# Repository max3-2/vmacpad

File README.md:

# vmacpad

A custom macro pad especially suited for FCPX and any other thing that needs
scrolling!

## ToDos from an old project

- Improve plate manufacture or / and increase switch opening size. The current
dimensioning is ok but fairly tight.
- Do the same for the stabs, if possible add at least 1mm left / right for the
stems

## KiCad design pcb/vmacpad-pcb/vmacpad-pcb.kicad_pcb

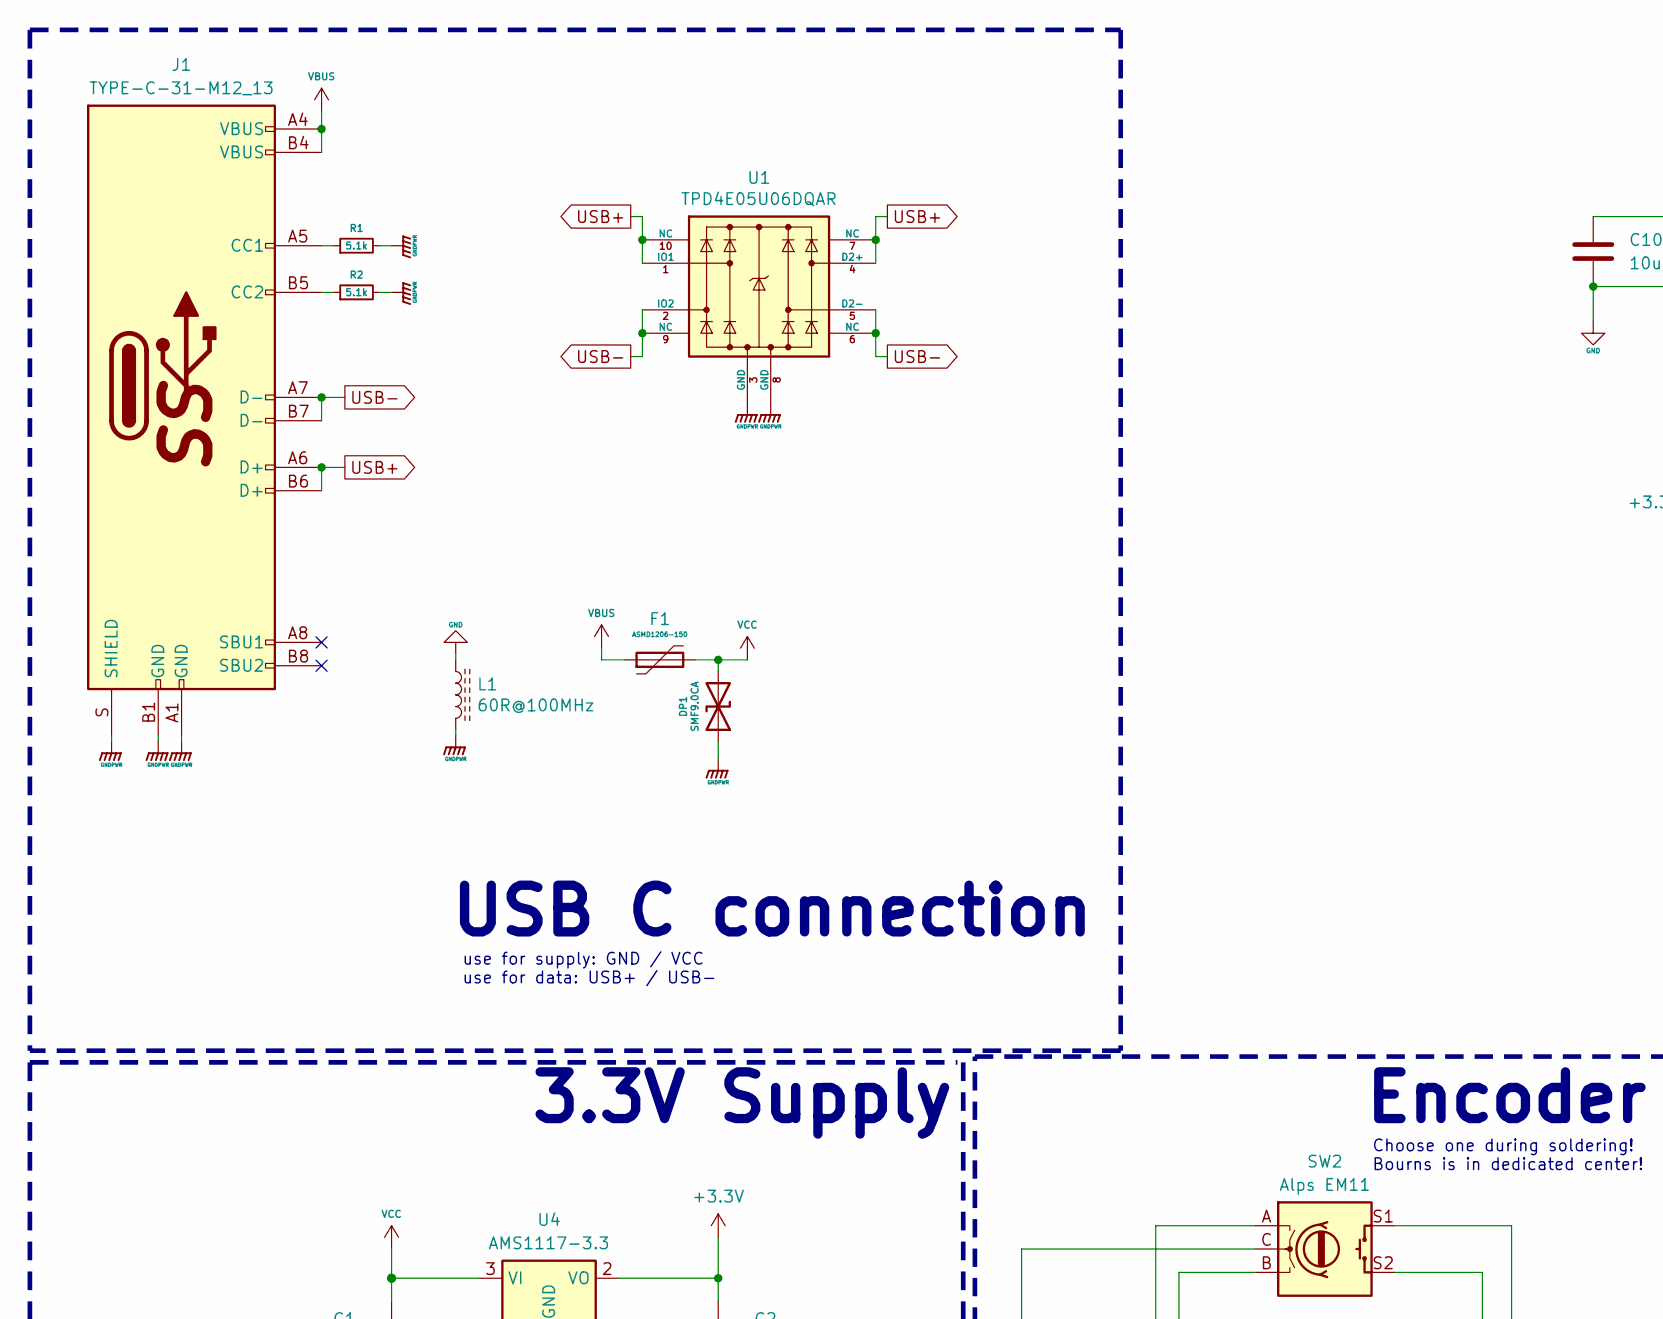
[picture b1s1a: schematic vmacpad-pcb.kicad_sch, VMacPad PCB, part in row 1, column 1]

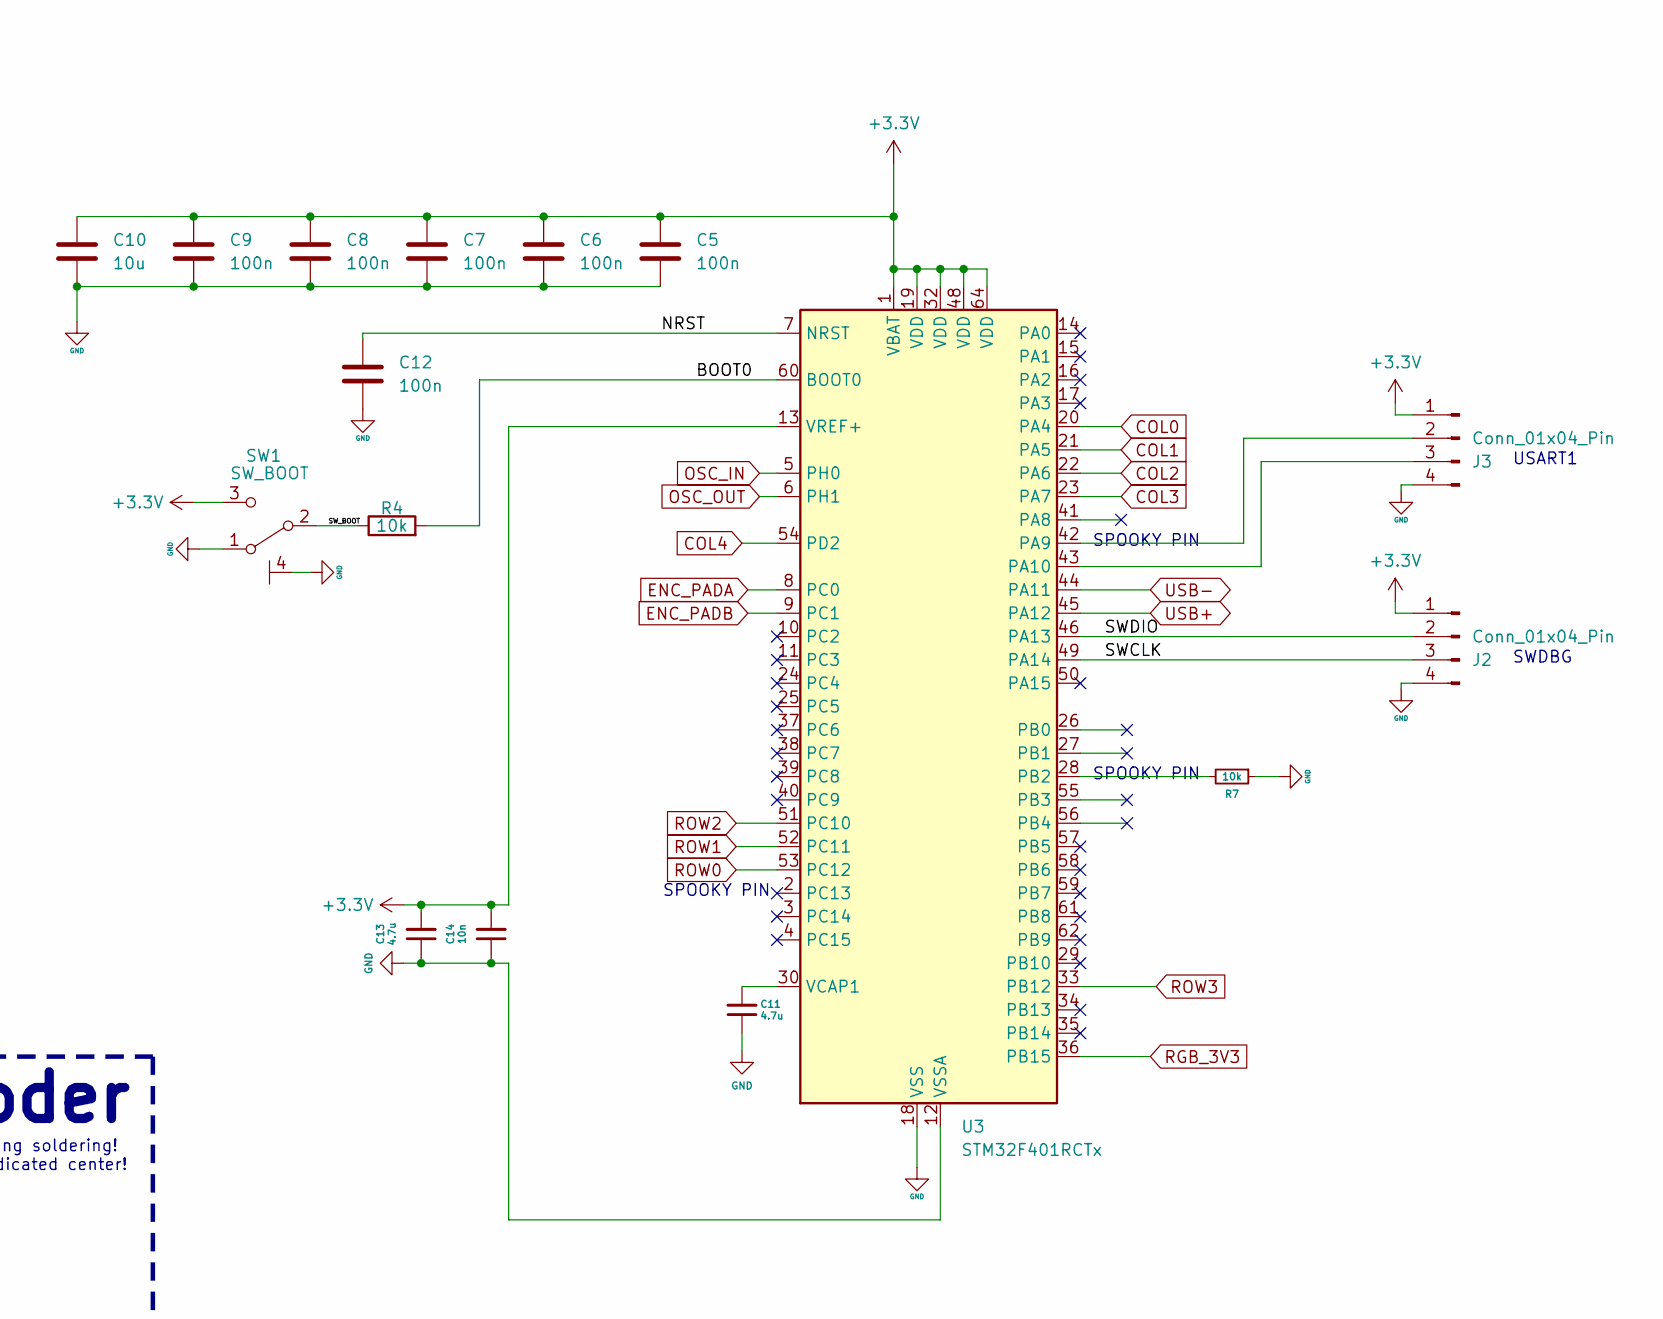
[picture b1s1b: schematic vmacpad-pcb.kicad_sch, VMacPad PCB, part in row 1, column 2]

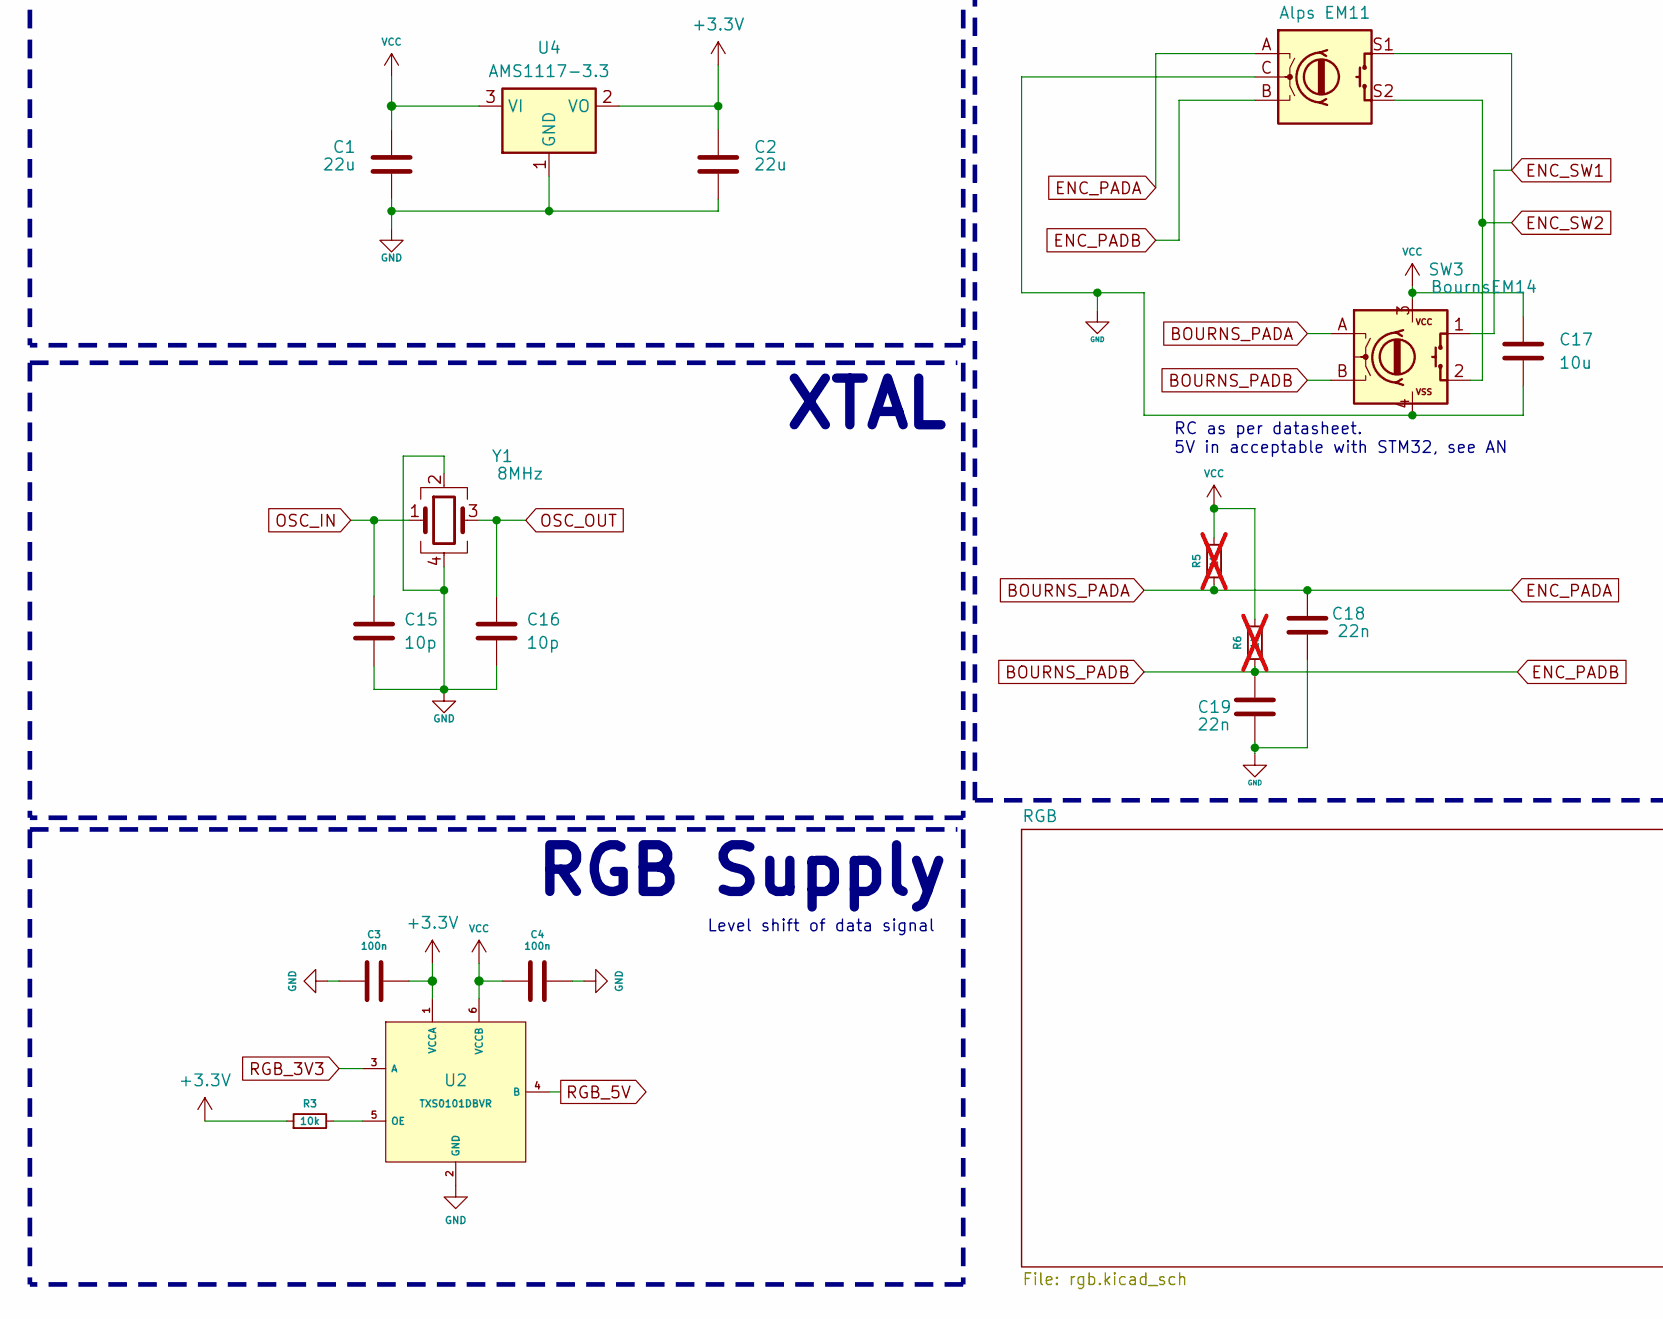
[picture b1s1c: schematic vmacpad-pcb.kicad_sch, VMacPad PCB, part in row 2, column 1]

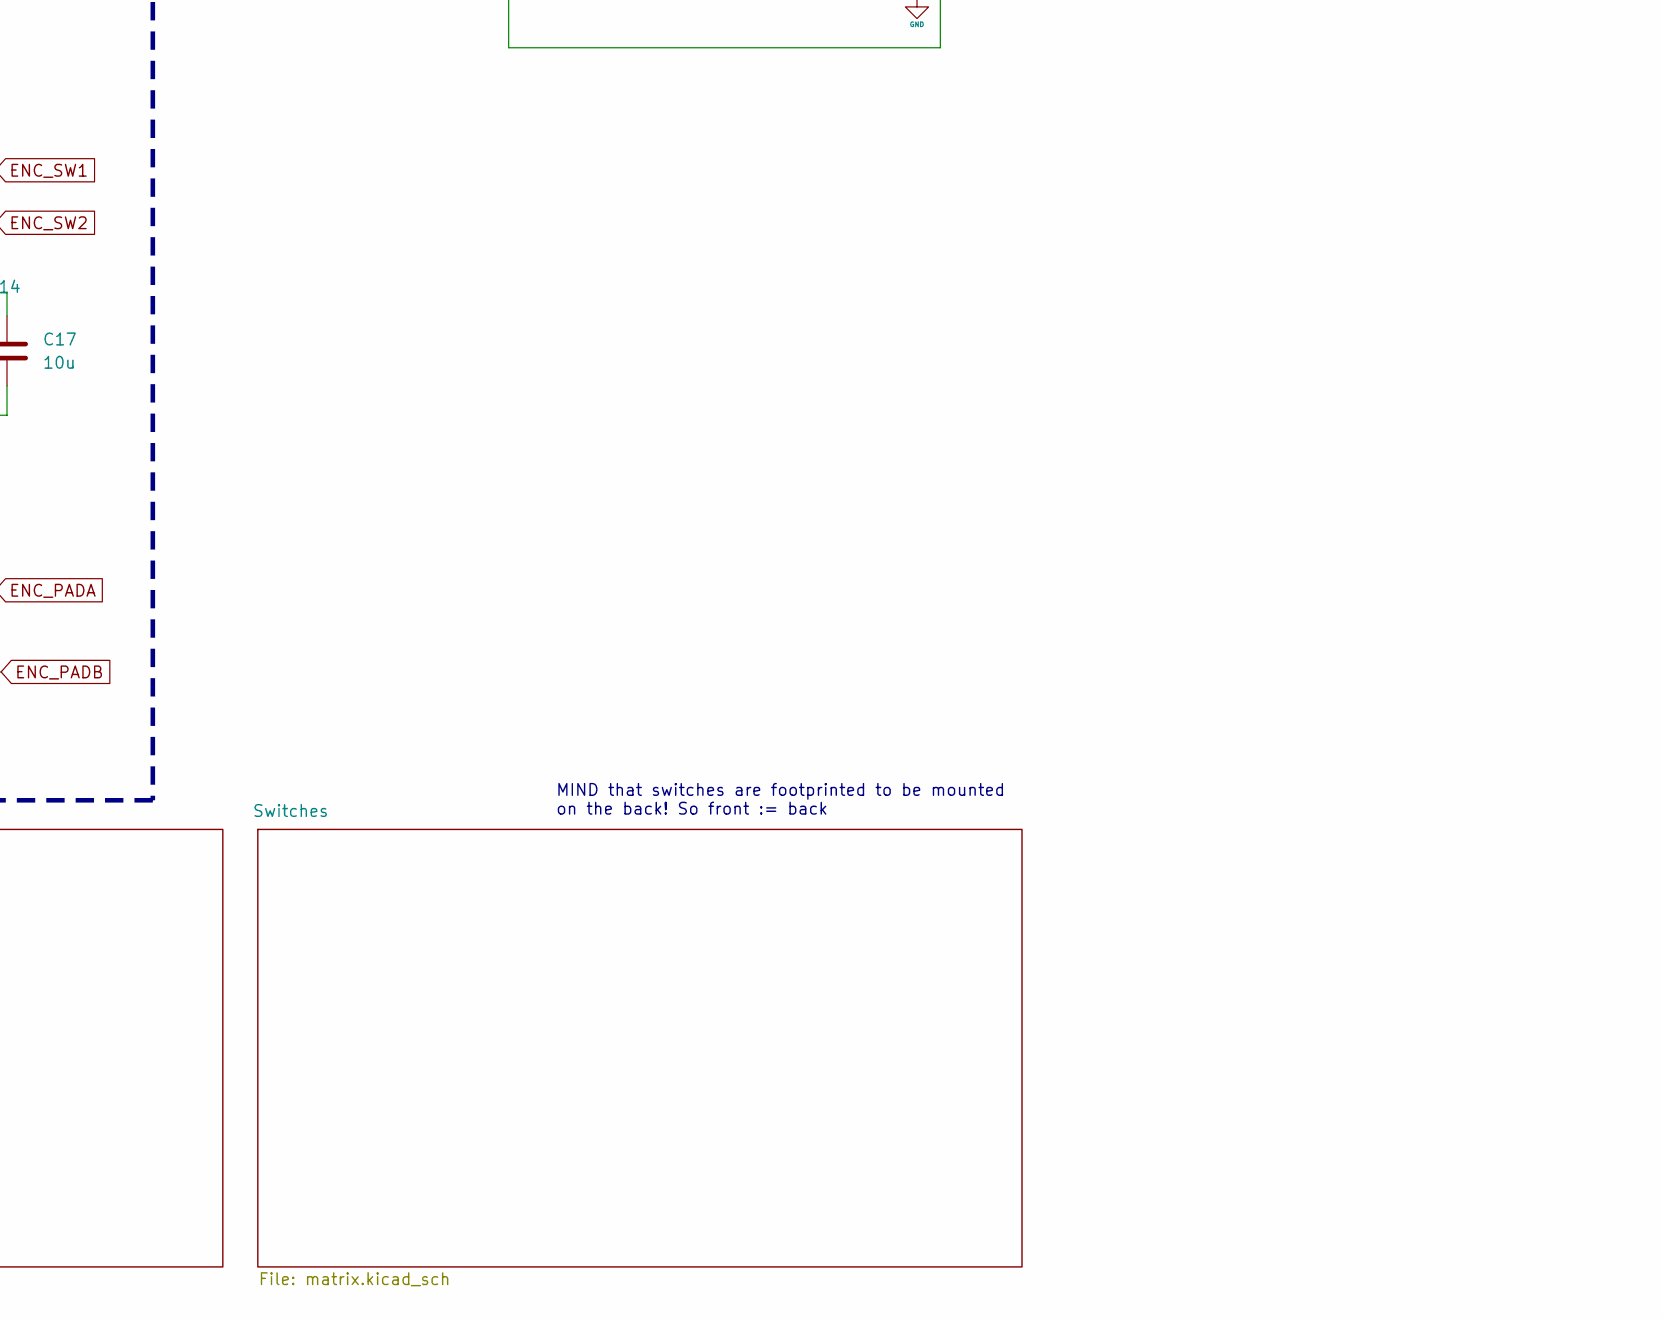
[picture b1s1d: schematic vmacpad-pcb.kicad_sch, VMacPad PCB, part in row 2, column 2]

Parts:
C1, C2: 22u; C_1206_3216Metric; LCSC Part No C2858005
C3, C4, C5, C6, C7, C8, C9, C12: 100n; C_0402_1005Metric; LCSC Part No C77020
C10, C17: 10u; C_0805_2012Metric; LCSC Part No C88484
C11, C13: 4.7u; C_0402_1005Metric; LCSC Part No C368809
C14: 10n; C_0402_1005Metric; LCSC Part No C60133
C15, C16: 10p; C_0402_1005Metric; LCSC Part No C115606
C18, C19: 22n; C_0805_2012Metric; LCSC Part No C51574
DP1: SMF9.0CA; D_SOD-123_Bidirectional; Manufacturer Part No SMF9.0CA; LCSC Part No C123799
F1: ASMD1206-150; Fuse_1206_3216Metric; Manufacturer Part No ASMD1206-150; LCSC Part No C883134
J1: TYPE-C-31-M12_13; TYPE-C-31-M-12; Manufacturer Part No TYPE-C-31-M-12; LCSC Part No C165948
J2, J3: Conn_01x04_Pin; PinHeader_1x04_P2.54mm_Vertical
L1: 60R@100MHz; L_1206_3216Metric; Manufacturer Part No MLB3216-600P4A(f); LCSC Part No C33600
R1, R2: 5.1k; R_0805_2012Metric; LCSC Part No C144526
R3, R4: 10k; R_0805_2012Metric; LCSC Part No C84376
R5, R6: 1k; R_0805_2012Metric; LCSC Part No C115316; not fitted
R7: 10k; R_0402_1005Metric; LCSC Part No C60490
SW1: SW_BOOT; SW_SPDT_PCM12; LCSC Part No C431540
SW2: Alps EM11; RotaryEncoder_Alps_EC11E-Switch_Vertical_H20mm
SW3: BournsEM14
U1: TPD4E05U06DQAR; USON-10_2.5x1.0mm_P0.5mm; Manufacturer Part No TPD4E05U06DQAR; LCSC Part No C138714
U2: TXS0101DBVR; SOT-23-6; Manufacturer Part Number TXS0101DBVR; LCSC Part No C132604
U3: STM32F401RCTx; LQFP-64_10x10mm_P0.5mm; LCSC Part No C74524
U4: AMS1117-3.3; SOT-223-3_TabPin2; LCSC Part No C6186
Y1: 8MHz; Crystal_SMD_3225-4Pin_3.2x2.5mm; LCSC Part No C400090

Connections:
+3.3V: C2.1, C3.2, C5.1, C6.1, C7.1, C8.1, C9.1, C10.1, C13.2, C14.2, J2.1, J3.1, R3.1, SW1.3 (C), U2.1 (VCCA), U3.1 (VBAT), U3.13 (VREF+), U3.19 (VDD), U3.32 (VDD), U3.48 (VDD), U3.64 (VDD), U4.2 (VO)
/BOOT0: R4.2, U3.60 (BOOT0)
/NRST: C12.1, U3.7 (NRST)
/SWCLK: J2.3, U3.49 (PA14)
/SWDIO: J2.2, U3.46 (PA13)
/SW_BOOT: R4.1, SW1.2 (B)
BOURNS_PADA: C18.1, R5.1, SW2.A, SW3.A, U3.8 (PC0)
BOURNS_PADB: C19.1, R6.1, SW2.B, SW3.B, U3.9 (PC1)
COL0: U3.20 (PA4); also elsewhere on the board
COL1: U3.21 (PA5); also elsewhere on the board
COL2: SW2.S2, SW3.2, U3.22 (PA6); also elsewhere on the board
COL3: U3.23 (PA7); also elsewhere on the board
COL4: U3.54 (PD2); also elsewhere on the board
ENC_SW1: SW2.S1, SW3.1; also elsewhere on the board
GND: C1.2, C2.2, C3.1, C4.2, C5.2, C6.2, C7.2, C8.2, C9.2, C10.2, C11.1, C12.2, C13.1, C14.1, C15.2, C16.2, C17.2, C18.2, C19.2, J2.4, J3.4, L1.1, R7.1, SW1.1 (A), SW1.4 (Fix), SW2.C, SW3.4 (VSS), U2.2 (GND), U3.12 (VSSA), U3.18 (VSS), U3.31 (VSS), U3.47 (VSS), U3.63 (VSS), U4.1 (GND), Y1.2, Y1.4; also elsewhere on the board
GNDPWR: DP1.1 (A1), J1.A1 (GND), J1.B1 (GND), J1.S (SHIELD), L1.2, R1.2, R2.2, U1.3 (GND), U1.8 (GND)
unnamed: J1.A5 (CC1), R1.1
unnamed: J1.B5 (CC2), R2.1
unnamed: J3.2, U3.42 (PA9)
unnamed: J3.3, U3.43 (PA10)
unnamed: R3.2, U2.5 (OE)
unnamed: R7.2, U3.28 (PB2)
unnamed: C11.2, U3.30 (VCAP1)
OSC_IN: C15.1, U3.5 (PH0), Y1.1
OSC_OUT: C16.1, U3.6 (PH1), Y1.3
RGB_3V3: U2.3 (A), U3.36 (PB15)
RGB_5V: U2.4 (B); also elsewhere on the board
ROW0: U3.53 (PC12); also elsewhere on the board
ROW1: U3.52 (PC11); also elsewhere on the board
ROW2: U3.51 (PC10); also elsewhere on the board
ROW3: U3.33 (PB12); also elsewhere on the board
USB+: J1.A6 (D+), J1.B6 (D+), U1.1 (IO1), U1.4 (D2+), U1.7 (NC), U1.10 (NC), U3.45 (PA12)
USB-: J1.A7 (D-), J1.B7 (D-), U1.2 (IO2), U1.5 (D2-), U1.6 (NC), U1.9 (NC), U3.44 (PA11)
VBUS: F1.1, J1.A4 (VBUS), J1.B4 (VBUS)
VCC: C1.1, C4.1, C17.1, DP1.2 (A2), F1.2, R5.2, R6.2, SW3.3 (VCC), U2.6 (VCCB), U4.3 (VI); also elsewhere on the board

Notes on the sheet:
use for supply: GND / VCC use for data: USB+ / USB-
SWDBG
USART1
XTAL
Level shift of data signal
Choose one during soldering! Bourns is in dedicated center!
RGB Supply
RC as per datasheet. 5V in acceptable with STM32, see AN
Encoder
SPOOKY PIN
USB C connection
MIND that switches are footprinted to be mounted on the back! So front := back
3.3V Supply

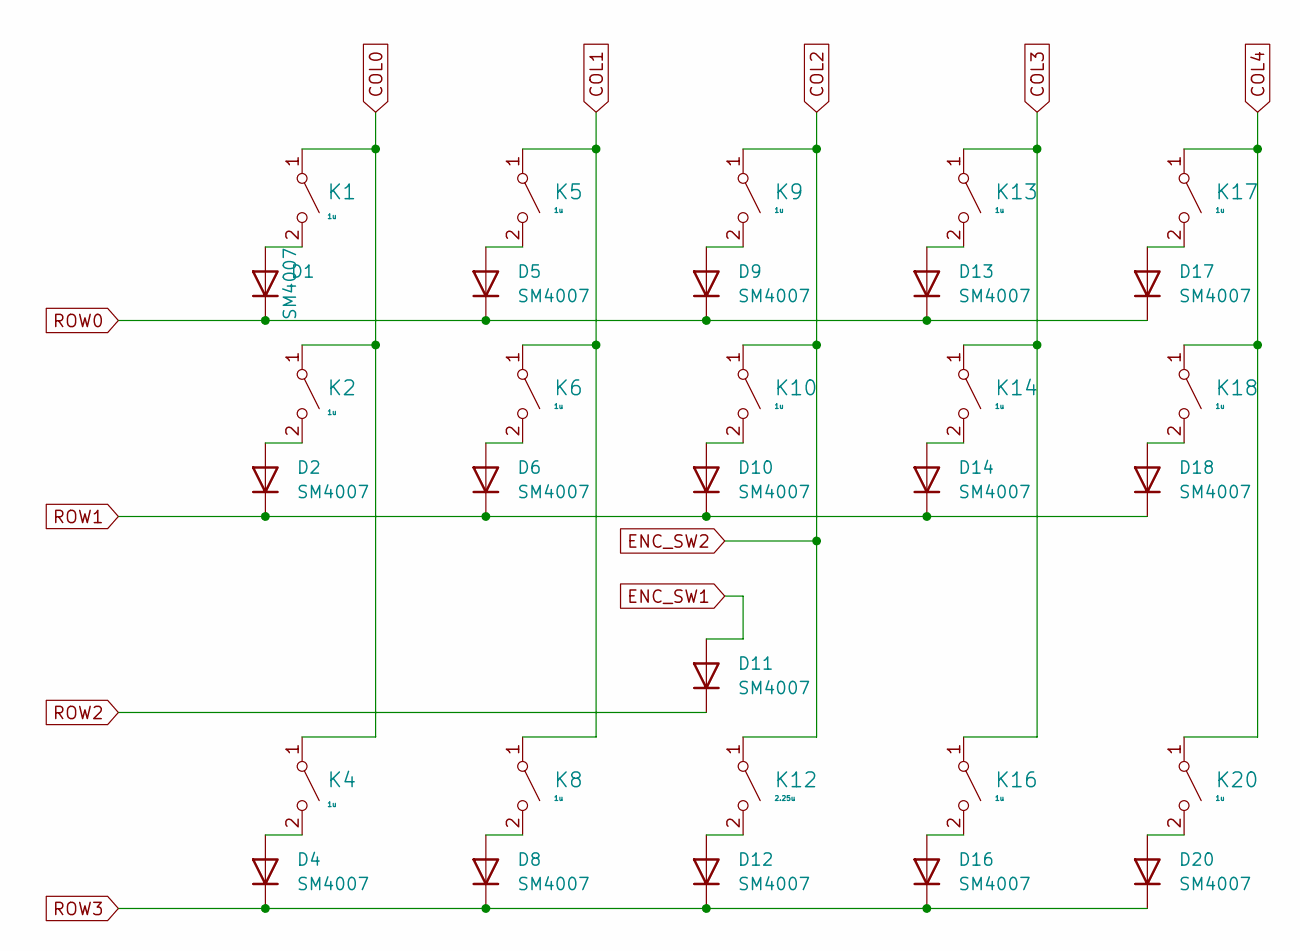
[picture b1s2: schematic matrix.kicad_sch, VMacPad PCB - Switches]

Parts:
D1, D2, D4, D5, D6, D8, D9, D10, D11, D12, D13, D14, D16, D17, D18, D20: SM4007; D_SOD-123F; LCSC Part No C64898
K1, K2, K4, K5, K6, K8, K9, K10, K13, K14, K16, K17, K18, K20: 1u; MX100H; LCSC Part No C5156480
K12: 2.25u; MX225HR; LCSC Part No C5156480

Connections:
COL0: K1.1 (A), K2.1 (A), K4.1 (A); also elsewhere on the board
COL1: K5.1 (A), K6.1 (A), K8.1 (A); also elsewhere on the board
COL2: K9.1 (A), K10.1 (A), K12.1 (A); also elsewhere on the board
COL3: K13.1 (A), K14.1 (A), K16.1 (A); also elsewhere on the board
COL4: K17.1 (A), K18.1 (A), K20.1 (A); also elsewhere on the board
ENC_SW1: D11.2 (A); also elsewhere on the board
unnamed: D1.2 (A), K1.2 (B)
unnamed: D2.2 (A), K2.2 (B)
unnamed: D4.2 (A), K4.2 (B)
unnamed: D5.2 (A), K5.2 (B)
unnamed: D6.2 (A), K6.2 (B)
unnamed: D8.2 (A), K8.2 (B)
unnamed: D9.2 (A), K9.2 (B)
unnamed: D10.2 (A), K10.2 (B)
unnamed: D12.2 (A), K12.2 (B)
unnamed: D13.2 (A), K13.2 (B)
unnamed: D14.2 (A), K14.2 (B)
unnamed: D16.2 (A), K16.2 (B)
unnamed: D17.2 (A), K17.2 (B)
unnamed: D18.2 (A), K18.2 (B)
unnamed: D20.2 (A), K20.2 (B)
ROW0: D1.1 (K), D5.1 (K), D9.1 (K), D13.1 (K), D17.1 (K); also elsewhere on the board
ROW1: D2.1 (K), D6.1 (K), D10.1 (K), D14.1 (K), D18.1 (K); also elsewhere on the board
ROW2: D11.1 (K); also elsewhere on the board
ROW3: D4.1 (K), D8.1 (K), D12.1 (K), D16.1 (K), D20.1 (K); also elsewhere on the board

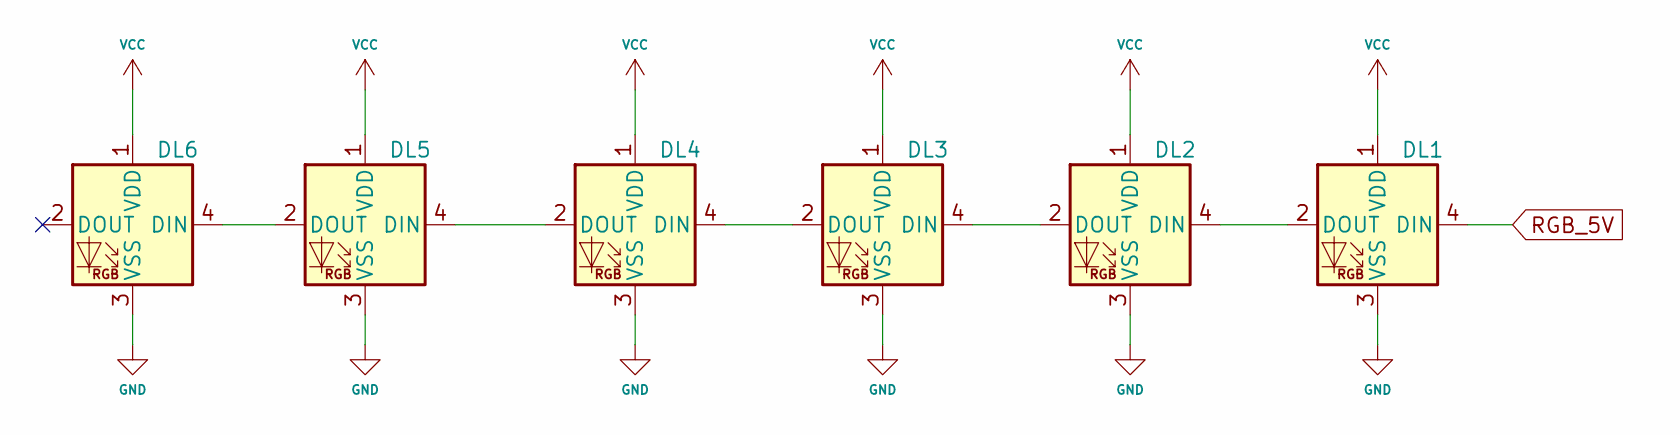
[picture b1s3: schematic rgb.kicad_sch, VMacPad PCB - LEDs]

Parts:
DL1, DL2, DL3, DL4, DL5, DL6: WS2812B; LED_WS2812B_PLCC4_5.0x5.0mm_P3.2mm; LCSC Part No C2874885

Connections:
GND: DL1.3 (VSS), DL2.3 (VSS), DL3.3 (VSS), DL4.3 (VSS), DL5.3 (VSS), DL6.3 (VSS); also elsewhere on the board
unnamed: DL1.2 (DOUT), DL2.4 (DIN)
unnamed: DL2.2 (DOUT), DL3.4 (DIN)
unnamed: DL3.2 (DOUT), DL4.4 (DIN)
unnamed: DL4.2 (DOUT), DL5.4 (DIN)
unnamed: DL5.2 (DOUT), DL6.4 (DIN)
RGB_5V: DL1.4 (DIN); also elsewhere on the board
VCC: DL1.1 (VDD), DL2.1 (VDD), DL3.1 (VDD), DL4.1 (VDD), DL5.1 (VDD), DL6.1 (VDD); also elsewhere on the board

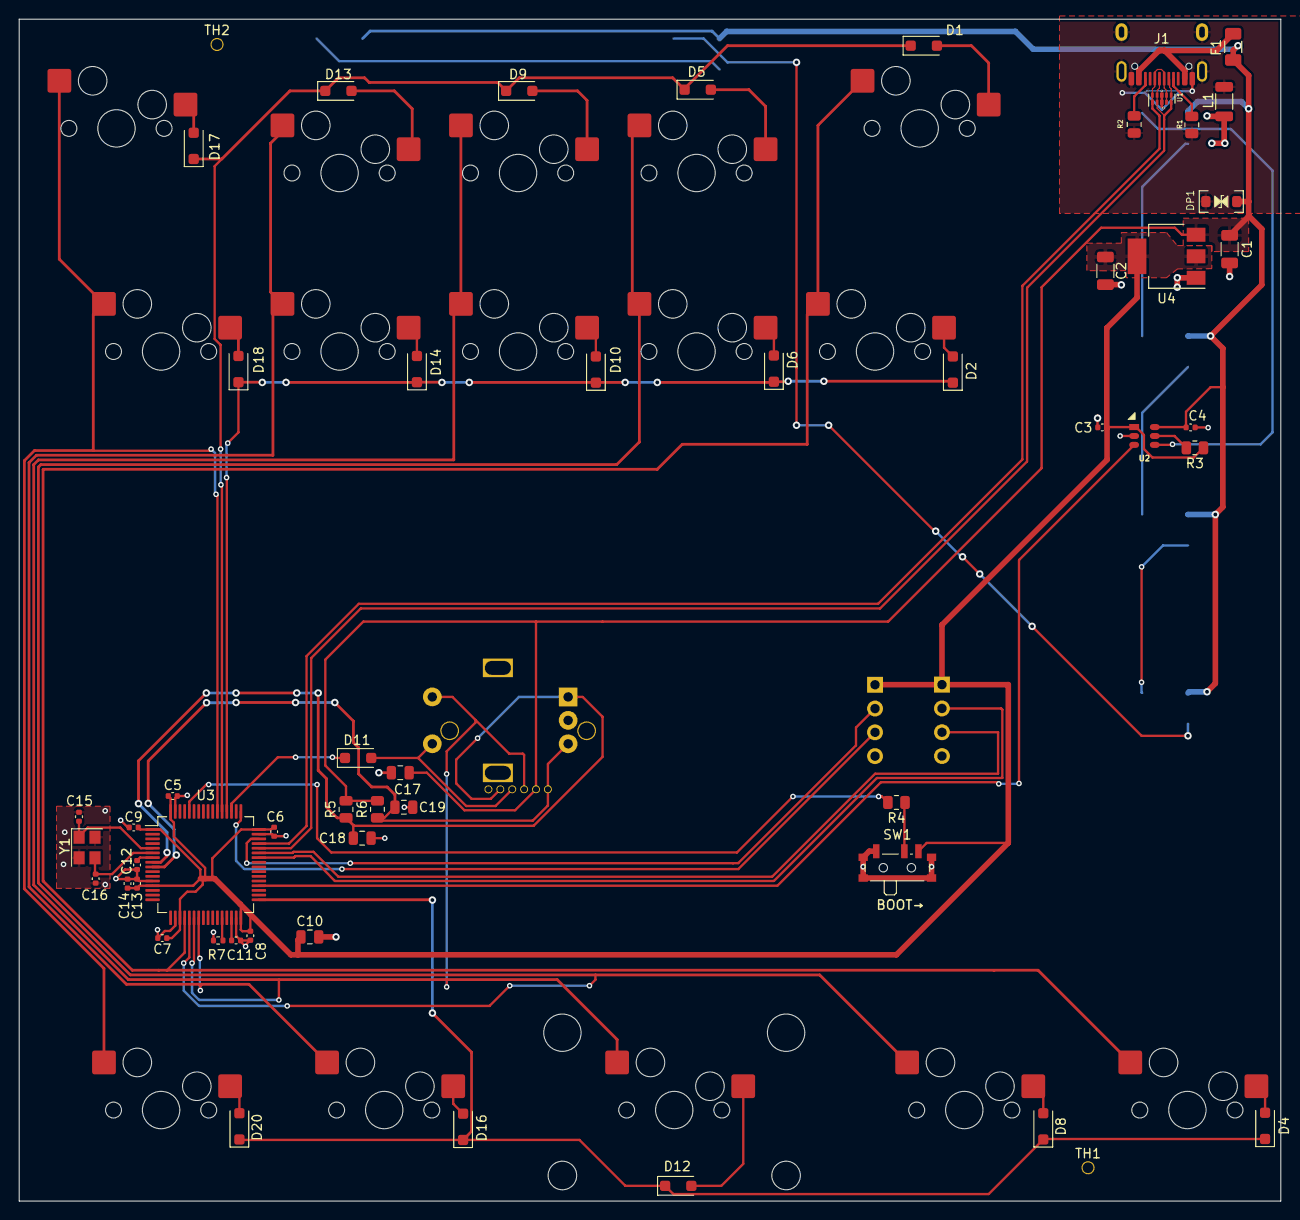
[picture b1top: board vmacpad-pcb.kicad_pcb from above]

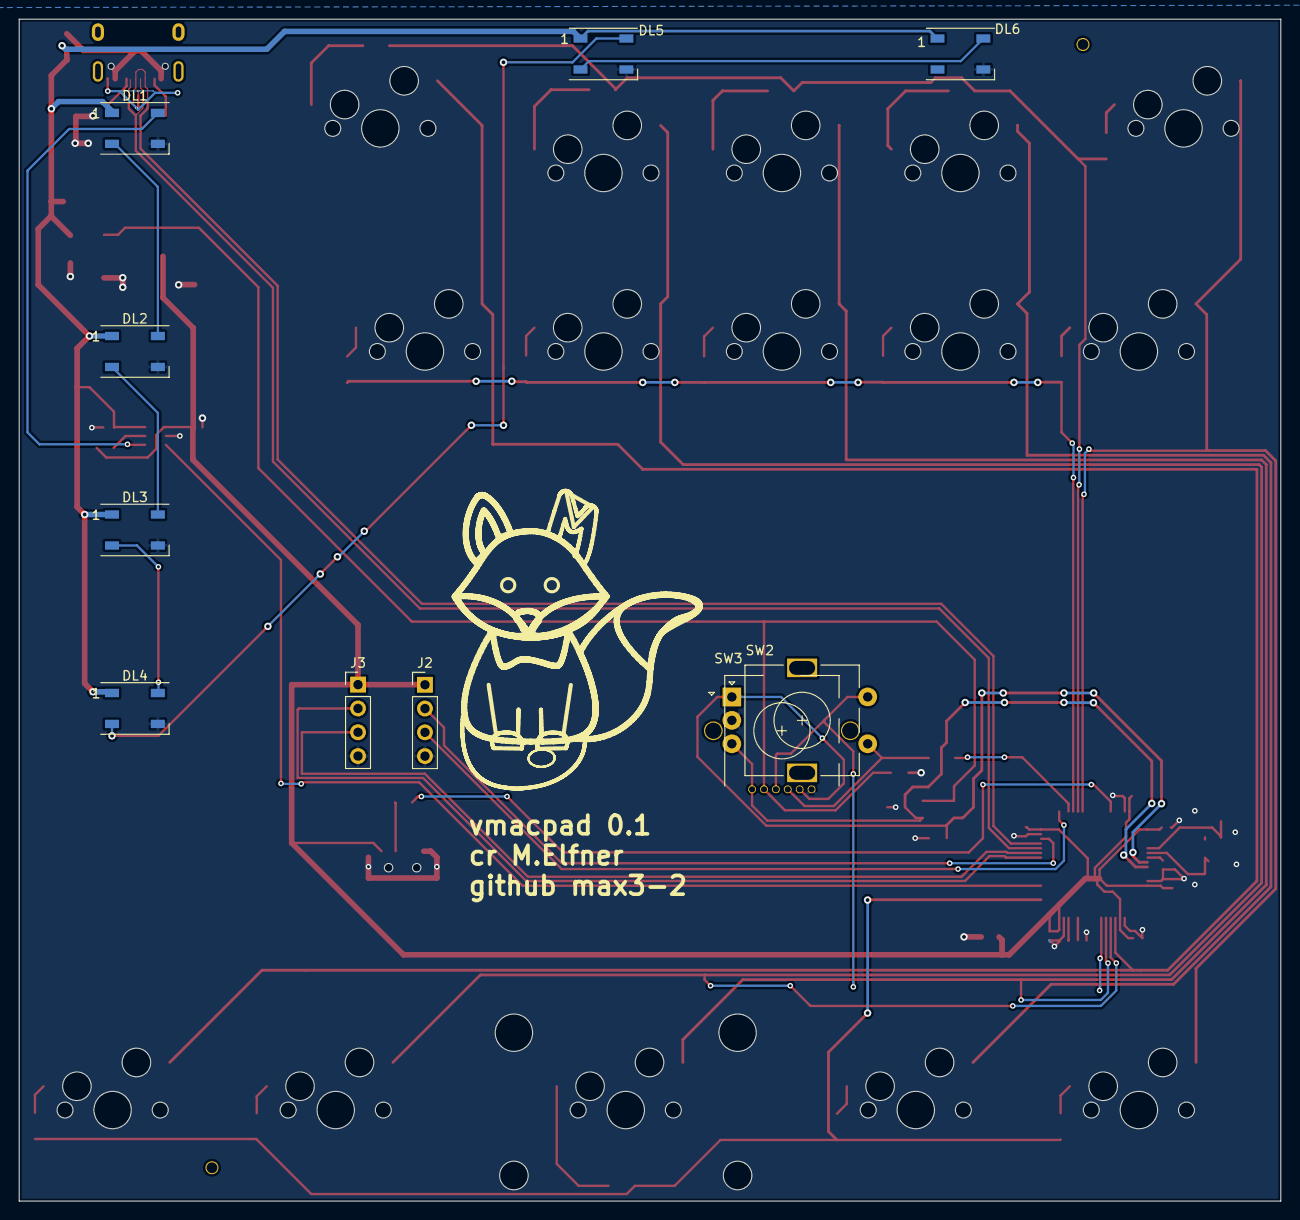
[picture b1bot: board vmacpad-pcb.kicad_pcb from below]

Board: 2 copper layers, 134.7 x 126.1 mm, 79 parts (10 on the bottom side), 55 nets.

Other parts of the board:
TH1, TH2: jlcpcb_tooling

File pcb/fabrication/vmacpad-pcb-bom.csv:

"Comment","Designator","Footprint","LCSC"
"22u","C1,C2","Capacitor_SMD:C_1206_3216Metric","C2858005"
"10u","C10,C17","Capacitor_SMD:C_0805_2012Metric","C88484"
"4.7u","C11,C13","Capacitor_SMD:C_0402_1005Metric","C368809"
"10n","C14","Capacitor_SMD:C_0402_1005Metric","C60133"
"10p","C15,C16","Capacitor_SMD:C_0402_1005Metric","C115606"
"22n","C18,C19","Capacitor_SMD:C_0805_2012Metric","C51574"
"100n","C3,C4,C5,C6,C7,C8,C9,C12","Capacitor_SMD:C_0402_1005Metric","C77020"
"SM4007","D1,D2,D4,D5,D6,D8,D9,D10,D11,D12,D13,D14,D16,D17,D18,D20","Diode_SMD:D_SOD-123F","C64898"
"SMF9.0CA","DP1","Acheron_Components:D_SOD-123_Bidirectional","C123799"
"ASMD1206-150","F1","Fuse:Fuse_1206_3216Metric","C883134"
"TYPE-C-31-M12_13","J1","Acheron_Connectors:TYPE-C-31-M-12","C165948"
"60R@100MHz","L1","Inductor_SMD:L_1206_3216Metric","C33600"
"5.1k","R1,R2","Resistor_SMD:R_0805_2012Metric","C144526"
"10k","R3,R4","Resistor_SMD:R_0805_2012Metric","C84376"
"10k","R7","Resistor_SMD:R_0402_1005Metric","C60490"
"SW_BOOT","SW1","Button_Switch_SMD:SW_SPDT_PCM12","C431540"
"TPD4E05U06DQAR","U1","Package_SON:USON-10_2.5x1.0mm_P0.5mm","C138714"
"TXS0101DBVR","U2","Acheron_Components:SOT-23-6","C132604"
"STM32F401RCTx","U3","Package_QFP:LQFP-64_10x10mm_P0.5mm","C74524"
"AMS1117-3.3","U4","Package_TO_SOT_SMD:SOT-223-3_TabPin2","C6186"
"16MHz","Y1","Crystal:Crystal_SMD_3225-4Pin_3.2x2.5mm","C112972"

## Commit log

2023-08-06 Encoder 1 3d model
2023-08-06 PCB Initial work
2023-08-06 Add initial layout
2023-08-08 Creating the PCB and additional parts
2023-08-12 Schematic Rev 1 done
2023-08-13 Finalizing PCB
2023-08-14 Final tweaks
2023-08-14 Add tooling holes
2023-08-14 Fix properties
2023-08-14 Fixes to part numbers and production
2023-08-14 Added initial FAB
2023-08-16 Fix power trace width
2023-08-16 Final v0.1 fab
2023-08-18 Add Logo
2023-08-18 Add plate and pcb 3d, fix models and export
2023-09-02 Fix minor placements
2023-09-02 Fix power tracks
2023-09-02 Change HSE to 8MHz
2023-09-02 FIX USB connection
2023-09-02 Improve USB component placement
